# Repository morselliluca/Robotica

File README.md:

# Robotica

SE NON AVETE VOGLIA DI LEGGERE A FINE README CI SONO LE INFORMAZZIONI PER CONTTATARCI

Tutti i ptogetti robotica del Gruppo DKV Lab<br/>
Siamo un gruppo di 2 persone dell'Itis rossi che hanno partecipato alla Robocup per 4 anni consecutivi con questi progetti.<br/>
il gruppo è formato da:

	Luca Morselli
		-Arduino e Teensyduino:
			-Data collection -> lettura sensori di calore, ultrasuono, riflesso, encoder
			-Serial and comunication -> comunicazione in seriale tra arduino / teensy e Raspberry
			-Movement -> libreria e calibrazione driver e motori dc
		-Pcb design 
		-Mechanical part design
		
	Luca Barban:
		-On Raspberry:
			-Opencv -> riconoscimento caratteri e colori
			-Navigation -> navigazione della mappa
			-Mapping -> creazione della mappa partendo da ultrasuoni o lidar
			-Data Collection -> salvare i dati sulla mappa del nero calore lettere ecc.
			-Serial and comunication -> comunicazione in seriale tra arduino / teensy e Raspberry
			
Cosa troverete all'interno di questa repository:

All'interno di 1. lego line troverete (Line):

	/programmi
		Il codice per la rescue line per un EV3 della lego
		/programmi/Blocchi
			Dei Blocchi custom per leggere il riflesso RGB separatamente da i sensori Stock della lego

All'inerno di 2. project manta troverete (Maze):

	/documentazione
		Un foglio xsl (foglio di calcolo) con tutti i pinout dell'arduino mega, nano e raspberry 
		
	/pcb
		Le Pcb logic e Power usate per il robot + i file gerber per ordinarli
		
	/programma
		/programma/arduino
			/programma/arduino/mega
				il programma per l'arduino mega
			/programma/arduino/nano
				il programma per l'arduino nano
			/programma/arduino/test
				programmi di test vari
		
		/programma/rsby
			programma di test per la raspberry
	
	/scocca
		/scocca/3d
			pezzi da stampare 3d per la scocca (non utilizzati per l'ultima verisone )
		/scocca/logo
			il logo del team
		/scocca/ruote
			ruote da tagliare al laser (non le consiglio, compratele fatte bene Pololu o simili)
		/scocca/taglio
			la scocca del robot da tagliare al laser 
				bello = il piu recente
				manta = delle prove 
				cobra = il primo tentativo
				
	lista.xls 
		la lista dei pezzi che compongono il robot

All'inerno di 3. project Hive troverete (Maze):

	/cagacubi
		le varie versioni del hopper per buttare giu i cubi
		
	/documentazione
		la varia documentazione per tutti i pezzi del robot +  i vari modelli 3d + regole
	
	/foto
		delle foto del robot renderizzato
	
	/pcb 
		file pdf delle schematiche delle 2 pcb del robot + i file gerber per ordinarli
	
	/programma
		/programma/teensy
			il programma per la teensy per interfacciarsi a ros
		/programma/test
			test vari per la teensy e i sensori
	
	/ros documentation
		buona fortuna ragazzi, questo e l'unico pezzo di documentazione ti ros olte il sito ufficiale fatto da cani
	
	/scocca
		disegni di fuzion della scocca del robot per il taglio a laser
	
	/taglio
		progetti in dxf pronti per il taglio laser
		
	Lista.xls
		la lista dei pezzi che compongono il robot

All'inerno di 4. project Help troverete (Line, in aiuto al team A.L.D.O. per i modniali di robotica):

	/La scocca in 3d per la line
	
	/I modelli dai pezzi scelti

Faq:

E presente anche una ide di arduino munita di Teensyduino, rosserial e tutte le librerie da noi utilizzate.

Le parti di raspberry degli ultimi 2 progetti mancano e verra aggiunta solo quella dell'ultimo progetto in quanto quella di Manta e stata persa.

I pezzi per il taglio laser sono stati provati principalmente in legno (pippo), plexiglass ed alluminio

I pezzi stampati sono sati stampati solo con stampanti 3d a filamento in quanto della a resina non funzionava (prusa MK.3)

Il grosso dei pezzi e stato acquistato da Aliexpress

Nella lista di Manta ci sono i driver dei motori cinesi NON COMPRATELI si bruciano subito prendete i pololu anche se costano di piu valgono la spesa

Non usate amg8833 come in Manta costano tanto e non e possibile cambiare l'indirizzo i2c nella libreria per leggerli in maniera semplice noi abbiamo usato 2 arduini in piu per questo motvo (i nano), la soluzione migliore e acquistare gli mlx90614

Le batterie consiglio Lipo o 18650 almeno una 3s per portare la tensione intorno i 12v () noi usiamo 2 2s in serie

Consiglio di usare ruote e non cingoli

Consiglio motori con encoder tornano utili per contare i giri che ha fatto la ruota

Per collegare raspberry ad arduino o simili usate la seriale e usate direttamente la porta USB poer evitare di bruciarlo in quanto la maggior parte degli arduino sono a 5v e la raspby supporta solo 3.3v

Quando usate i driver della pololu come MC33926 portate il pin EN -> HIGH e i pin PWM(Negato)/D1 -> Low

I pin INA e INB sono usati per la direzione, vanno messi uno in HIGH uno in LOW 

Da prova_v17 sul progetto Hive le funzioni hanno un timing e vengono eseguite esattamente ogni N millisecondi (la funzione si trova all'interno del void loop)<br/>
	-Odom viene mandata 100HZ<br/>
	-velocita e encoder sono calcolati 1000HZ<br/>

Source:<br/>

Sensori di distanza arduino:<br/>
https://www.youtube.com/watch?v=6F1B_N6LuKw<br/>
https://dronebotworkshop.com/hc-sr04-ultrasonic-distance-sensor-arduino/<br/>

Libreria Pololu vnh5019, la base della libreria custom che troverete in/arduino-1.8.19/libraries/DriverDkv<br/>
https://github.com/pololu/dual-vnh5019-motor-shield<br/>
	
Tutorial per Rosserail + navigation:<br/>
https://www.youtube.com/watch?v=q1u_cC-5Sac<br/>
https://www.youtube.com/watch?v=HLLmV9LQoac<br/>

Ros in generale:<br/>
http://hotblackrobotics.github.io<br/>
https://automaticaddison.com<br/>

Ros navigation:<br/>
https://emanual.robotis.com/docs/en/platform/turtlebot3/learn/#books<br/>
http://wiki.ros.org/ROS/Installation<br/>
http://wiki.ros.org/catkin/Tutorials/create_a_workspace<br/>
http://wiki.ros.org/navigation/Tutorials/RobotSetup<br/>
http://wiki.ros.org/teb_local_planner<br/>
https://answers.ros.org/question/249216/rosserial-posearray-crashes-when-more-than-8-poses-are-used/<br/>

Mlx90614 come usarle e cambiare indirizzo:<br/>
https://www.instructables.com/Multiple-IR-Temperature-Sensors/<br/>
	
Il software per disegnare pcb che consiglio::<br/>
https://easyeda.com/editor<br/>
		
Dove ordinare le pcb online:<br/>
https://jlcpcb.com/<br/>
		
Dove ho ordinato i pezzi tagliati al laser in alluminio:<br/>
https://www.laserboost.com/en/create<br/>
	
Arduino ide (non la 2.0 che non funziona con teensyduino):<br/>
https://www.arduino.cc/en/software<br/>
			
Teensyduino:<br/>
https://www.pjrc.com/teensy/td_usage.html<br/>
https://www.pjrc.com/teensy/teensyduino.html<br/>
https://www.pjrc.com/teensy/td_pulse.html<br/>
https://www.pjrc.com/teensy/td_digital.html<br/>
https://www.pjrc.com/teensy/td_serial.html<br/>
https://www.pjrc.com/teensy/td_uart.html<br/>
		
Software Modellazione 3d (Fusion360 e gratis per gli studenti):<br/>	
https://www.autodesk.com/products/fusion-360/free-trial<br/>

NOTA:<br/>
Usare in maniera informativa nessuno di questi progetti e perfetto ma possono essere usati come una buona base per capire il funzionamento dei vari componenti<br/>
Siamo felici di aiutarvi per qualunque dubbio o perplessita<br/>

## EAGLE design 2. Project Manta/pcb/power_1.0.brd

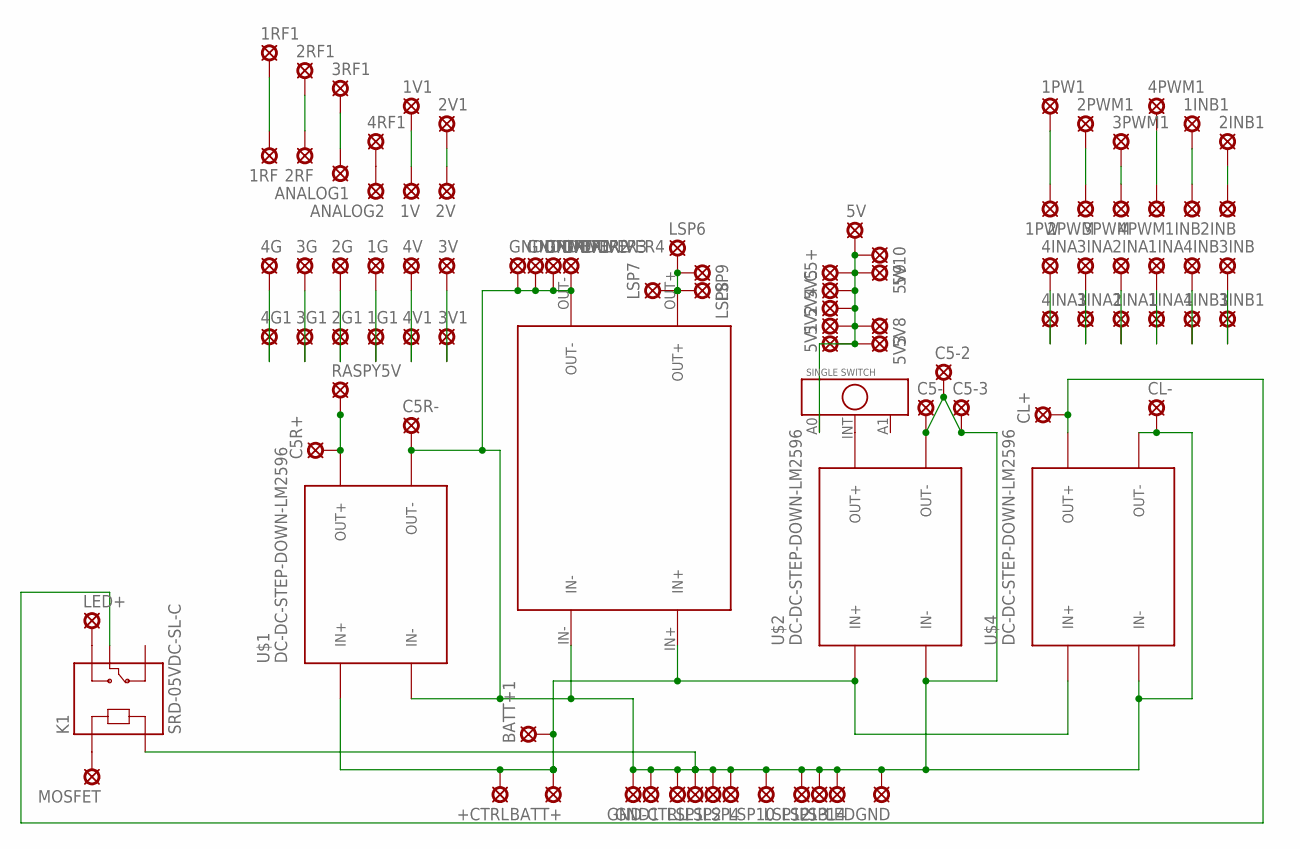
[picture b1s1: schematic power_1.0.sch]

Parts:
1G, 1G1, 1INA, 1INA1, 1INB, 1INB1, 1PW, 1PW1, 1RF, 1RF1, 1V, 1V1, 2G, 2G1, 2INA, 2INA1, 2INB, 2INB1, 2PWM, 2PWM1, 2RF, 2RF1, 2V, 2V1, 3G, 3G1, 3INA, 3INA1, 3INB, 3INB1, 3PWM, 3PWM1, 3RF1, 3V, 3V1, 4G, 4G1, 4INA, 4INA1, 4INB, 4INB1, 4PWM, 4PWM1, 4RF1, 4V, 4V1, 5V, 5V1, 5V2, 5V3, 5V4, 5V5, 5V8, 5V9, 5V10: LSP10
+CTRL: LSP10
-CTRL: LSP10
ANALOG1, ANALOG2: LSP10
BATT+, BATT+1: SE14
C5+, C5-, C5-2, C5-3, C5R+, C5R-: LSP10
CL+: LSP10
CL-: LSP10
GND, GND1: SE14
GNDDRIVER1, GNDDRIVER2, GNDDRIVER3, GNDDRIVER4: SE14
K1: SRD-05VDC-SL-C; RELAY_SRD-05VDC-SL-C
LED+: SE14
LEDGND: SE14
LSP1, LSP2, LSP4, LSP10, LSP12, LSP13, LSP14: LSP10
LSP6, LSP7, LSP8, LSP9: SE14
MOSFET: LSP10
RASPY5V: LSP10
U$1, U$2, U$4: DC-DC-STEP-DOWN-LM2596
U$3: DC-DCSTEPUP/DOWNBUCKCONVERTER
U$5: SINGE_SWITCH; SINGLE_SWITCH

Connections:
GND: -CTRL.MP, C5-.MP, C5-2.MP, C5-3.MP, C5R-.MP, CL-.MP, GND.MP, GND1.MP, GNDDRIVER1.MP, GNDDRIVER2.MP, GNDDRIVER3.MP, GNDDRIVER4.MP, K1.A2, LEDGND.MP, LSP1.MP, LSP2.MP, LSP4.MP, LSP10.MP, LSP12.MP, LSP13.MP, LSP14.MP, U$1.IN-, U$1.OUT-, U$2.IN-, U$2.OUT-, U$3.IN-, U$3.OUT-, U$4.IN-, U$4.OUT-
unnamed: U$2.OUT+, U$5.INT
unnamed: LSP6.MP, LSP7.MP, LSP8.MP, LSP9.MP, U$3.OUT+
unnamed: C5R+.MP, RASPY5V.MP, U$1.OUT+
unnamed: 5V.MP, 5V1.MP, 5V2.MP, 5V3.MP, 5V4.MP, 5V5.MP, 5V8.MP, 5V9.MP, 5V10.MP, C5+.MP, U$5.A0
unnamed: 4G.MP, 4G1.MP
unnamed: 3G.MP, 3G1.MP
unnamed: 2G.MP, 2G1.MP
unnamed: 1G.MP, 1G1.MP
unnamed: 4V.MP, 4V1.MP
unnamed: 3V.MP, 3V1.MP
unnamed: 2V.MP, 2V1.MP
unnamed: 1V.MP, 1V1.MP
unnamed: 4RF1.MP, ANALOG2.MP
unnamed: 3RF1.MP, ANALOG1.MP
unnamed: 2RF.MP, 2RF1.MP
unnamed: 1RF.MP, 1RF1.MP
unnamed: 1PW.MP, 1PW1.MP
unnamed: 2PWM.MP, 2PWM1.MP
unnamed: 4INA.MP, 4INA1.MP
unnamed: 3INA.MP, 3INA1.MP
unnamed: 2INA.MP, 2INA1.MP
unnamed: 1INA.MP, 1INA1.MP
unnamed: 4INB.MP, 4INB1.MP
unnamed: 3INB.MP, 3INB1.MP
unnamed: 3PWM.MP, 3PWM1.MP
unnamed: 4PWM.MP, 4PWM1.MP
unnamed: 1INB.MP, 1INB1.MP
unnamed: 2INB.MP, 2INB1.MP
unnamed: K1.NO, LED+.MP
unnamed: K1.A1, MOSFET.MP
unnamed: CL+.MP, K1.COM, U$4.OUT+
unnamed: +CTRL.MP, BATT+.MP, BATT+1.MP, U$1.IN+, U$2.IN+, U$3.IN+, U$4.IN+

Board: 2 copper layers, 96 parts (0 on the bottom side), 33 nets, no tracks yet.

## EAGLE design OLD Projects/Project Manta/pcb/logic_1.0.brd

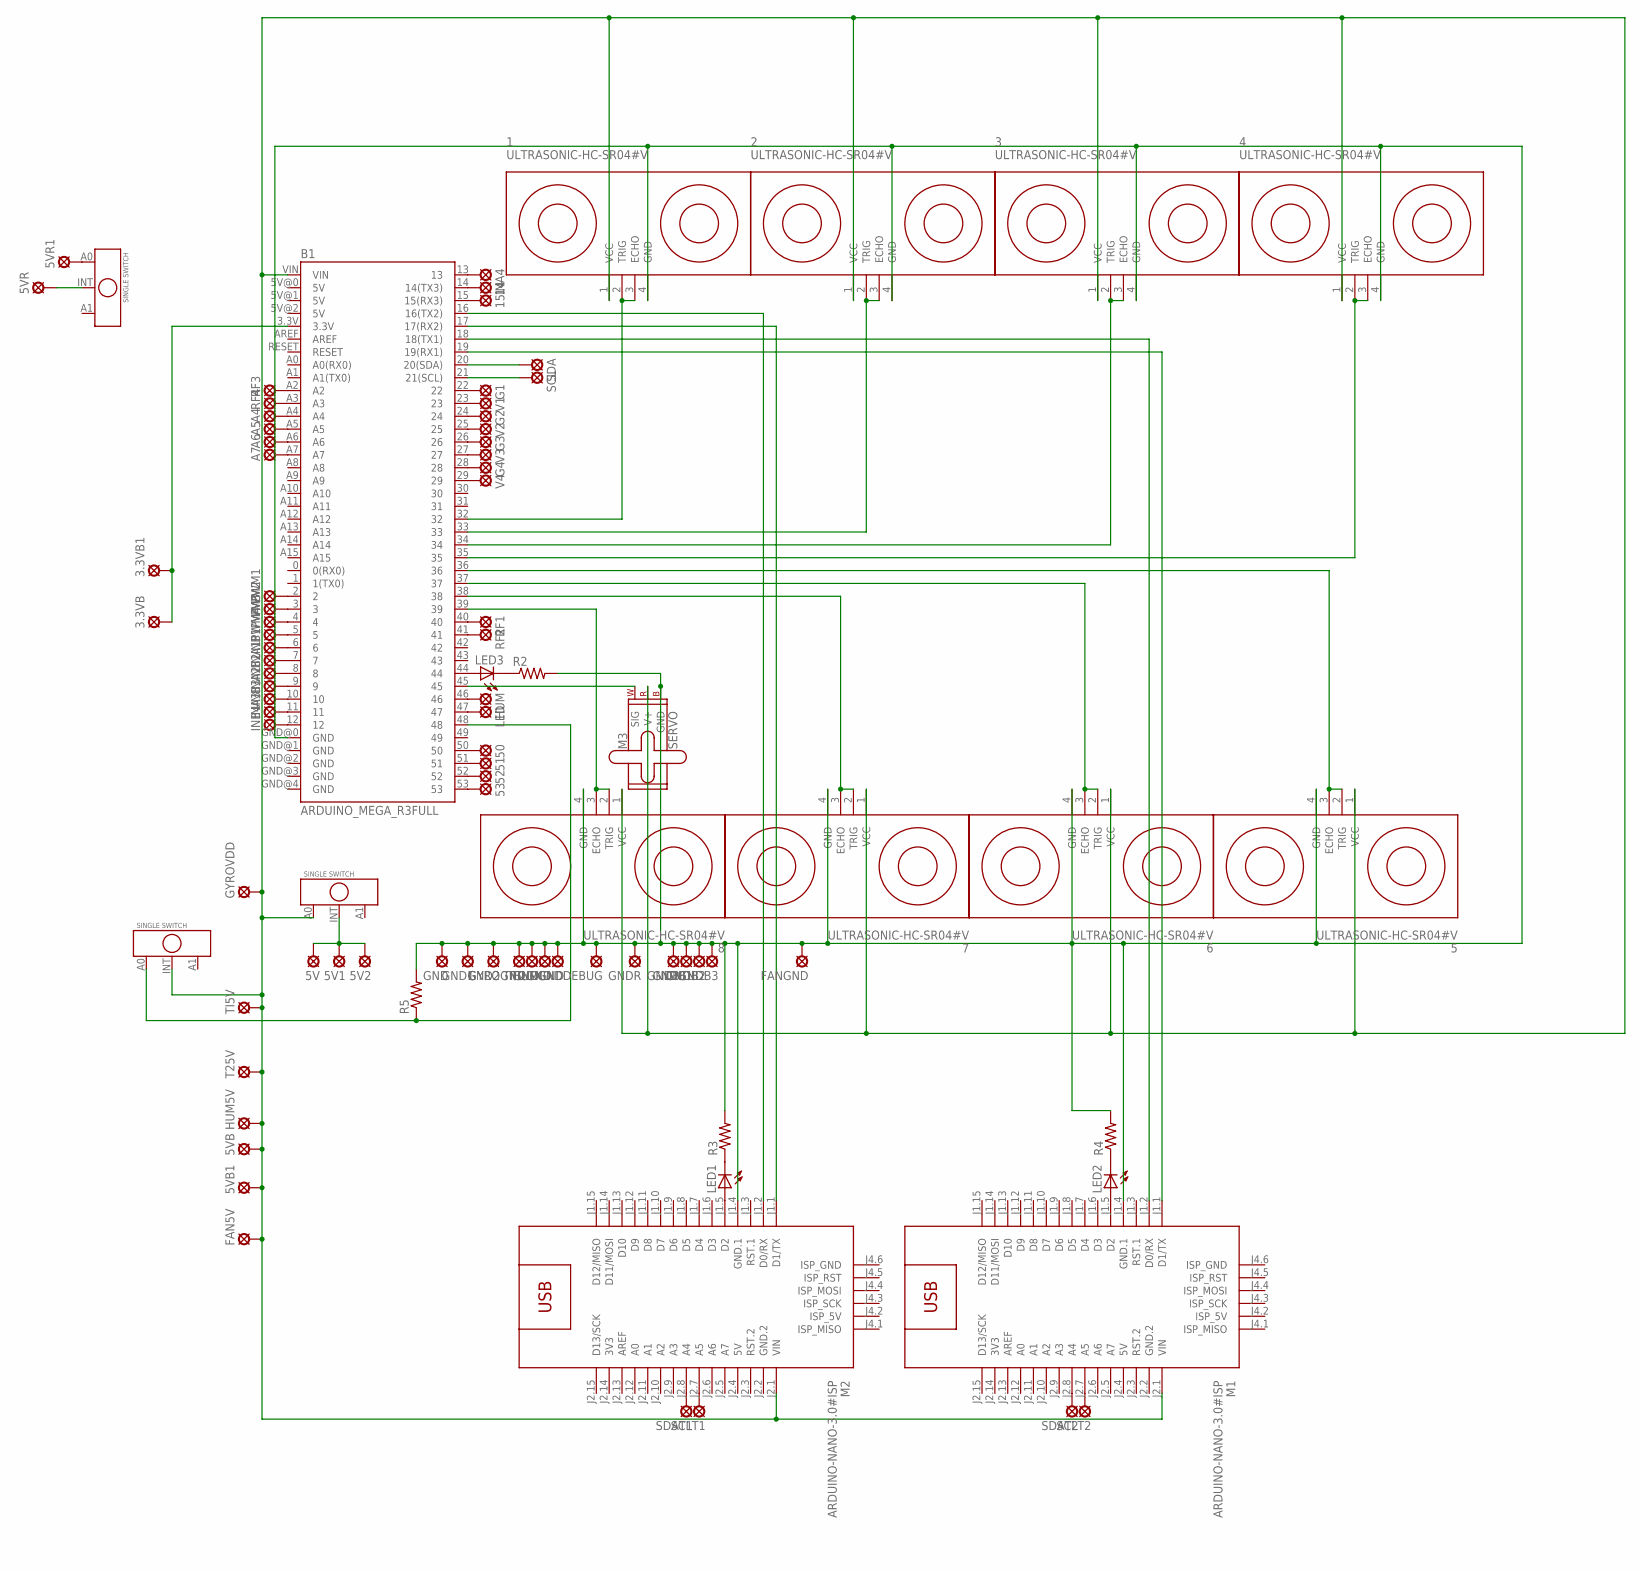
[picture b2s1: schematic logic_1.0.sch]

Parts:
1, 2, 3, 4, 5, 6, 7, 8: ULTRASONIC-HC-SR04#V
3.3VB, 3.3VB1, 5V, 5V1, 5V2, 5VB, 5VB1, 5VR, 5VR1, 14, 15, 50, 51, 52, 53: LSP10
A4, A5, A6, A7: LSP10
B1: ARDUINO_MEGA_R3FULL; ARDUINO_MEGA
FAN5V: LSP10
FANGND: LSP10
G1, G2, G3, G4: LSP10
GND, GND1, GND2: LSP10
GNDB, GNDB1, GNDB2, GNDB3: LSP10
GNDDEBUG: LSP10
GNDR: LSP10
GYROGND: LSP10
GYROVDD: LSP10
HUM, HUM5V: LSP10
HUMGND: LSP10
INA1, INA2, INA3, INA4: LSP10
INB1, INB2, INB3, INB4: LSP10
LED: LSP10
LED1, LED2, LED3: LED5MM
M1, M2: ARDUINO-NANO-3.0#ISP
M3: SERVO; 1X03
PWM1, PWM2, PWM3, PWM4: LSP10
R2, R3, R4, R5: R-US_0207/10; 0207/10
RF1, RF2, RF3, RF4: LSP10
SCL: LSP10
SCLT1, SCLT2: LSP10
SDA: LSP10
SDAT1, SDAT2: LSP10
T2GND, T25V: LSP10
TI5V: LSP10
TIGND: LSP10
U$1, U$2, U$3: SINGE_SWITCH; SINGLE_SWITCH
V1, V2, V3, V4: LSP10

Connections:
3V3: M1.J2.14 (3V3), M2.J2.14 (3V3)
5V: M1.J2.4 (5V), M2.J2.4 (5V)
GND: 1.4 (GND), 2.4 (GND), 3.4 (GND), 4.4 (GND), 5.4 (GND), 6.4 (GND), 7.4 (GND), 8.4 (GND), B1.GND@0 (GND), FANGND.MP, GND.MP, GND1.MP, GND2.MP, GNDB.MP, GNDB1.MP, GNDB2.MP, GNDB3.MP, GNDDEBUG.MP, GNDR.MP, GYROGND.MP, HUMGND.MP, M1.J1.4 (GND.1), M2.J1.4 (GND.1), M3.3 (GND), R2.2, R3.2, R4.2, R5.2, T2GND.MP, TIGND.MP
GND.2: M1.J2.2 (GND.2), M2.J2.2 (GND.2)
unnamed: 5VR1.MP, U$2.A0
unnamed: 5V.MP, 5V1.MP, 5V2.MP, U$1.INT
unnamed: B1.2, PWM1.MP
unnamed: B1.16 (16(TX2)), M2.J1.2 (D0/RX)
unnamed: B1.17 (17(RX2)), M2.J1.1 (D1/TX)
unnamed: B1.18 (18(TX1)), M1.J1.2 (D0/RX)
unnamed: B1.19 (19(RX1)), M1.J1.1 (D1/TX)
unnamed: 1.2 (TRIG), 1.3 (ECHO), B1.32
unnamed: 2.2 (TRIG), 2.3 (ECHO), B1.33
unnamed: 3.2 (TRIG), 3.3 (ECHO), B1.34
unnamed: 4.2 (TRIG), 4.3 (ECHO), B1.35
unnamed: 5.2 (TRIG), 5.3 (ECHO), B1.36
unnamed: 6.2 (TRIG), 6.3 (ECHO), B1.37
unnamed: 7.2 (TRIG), 7.3 (ECHO), B1.38
unnamed: 8.2 (TRIG), 8.3 (ECHO), B1.39
unnamed: B1.45, M3.1 (SIG)
unnamed: 1.1 (VCC), 2.1 (VCC), 3.1 (VCC), 4.1 (VCC), 5.1 (VCC), 5VB.MP, 5VB1.MP, 6.1 (VCC), 7.1 (VCC), 8.1 (VCC), B1.VIN, FAN5V.MP, GYROVDD.MP, HUM5V.MP, M1.J2.1 (VIN), M2.J2.1 (VIN), M3.2 (V+), T25V.MP, TI5V.MP, U$1.A0, U$3.INT
unnamed: B1.3, PWM2.MP
unnamed: B1.4, PWM3.MP
unnamed: B1.5, PWM4.MP
unnamed: B1.6, INB1.MP
unnamed: B1.7, INA1.MP
unnamed: B1.8, INB2.MP
unnamed: B1.9, INA2.MP
unnamed: B1.10, INB3.MP
unnamed: B1.11, INA3.MP
unnamed: B1.12, INB4.MP
unnamed: B1.13, INA4.MP
unnamed: B1.22, G1.MP
unnamed: B1.23, V1.MP
unnamed: B1.24, G2.MP
unnamed: B1.25, V2.MP
unnamed: B1.26, G3.MP
unnamed: B1.27, V3.MP
unnamed: B1.28, G4.MP
unnamed: B1.29, V4.MP
unnamed: B1.20 (20(SDA)), SDA.MP
unnamed: B1.21 (21(SCL)), SCL.MP
unnamed: B1.46, HUM.MP
unnamed: B1.47, LED.MP
unnamed: 3.3VB.MP, 3.3VB1.MP, B1.3.3V
unnamed: M2.J2.8 (A4), SDAT1.MP
unnamed: M2.J2.7 (A5), SCLT1.MP
unnamed: M1.J2.8 (A4), SDAT2.MP
unnamed: M1.J2.7 (A5), SCLT2.MP
unnamed: B1.40, RF1.MP
unnamed: B1.44, LED3.A
unnamed: B1.41, RF2.MP
unnamed: 5VR.MP, U$2.INT
unnamed: B1.A2, RF3.MP
unnamed: B1.A3, RF4.MP
unnamed: LED1.A, M2.J1.5 (D2)
unnamed: LED2.A, M1.J1.5 (D2)
unnamed: LED3.K (C), R2.1
unnamed: LED2.K (C), R4.1
unnamed: LED1.K (C), R3.1
unnamed: 50.MP, B1.50
unnamed: 51.MP, B1.51
unnamed: 52.MP, B1.52
unnamed: A6.MP, B1.A6
unnamed: A7.MP, B1.A7
unnamed: A4.MP, B1.A4
unnamed: A5.MP, B1.A5
unnamed: 53.MP, B1.53
unnamed: B1.48, R5.1, U$3.A0
unnamed: 14.MP, B1.14 (14(TX3))
unnamed: 15.MP, B1.15 (15(RX3))

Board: 2 copper layers, 92 parts (1 on the bottom side), 71 nets, no tracks yet.

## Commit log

2021-12-20 Version 1
2021-12-24 nuova scocca
2021-12-24 render
2021-12-31 sistemato roba
2022-01-22 change
2022-01-26 opsy
2022-02-02 test
2022-02-17 i cazzi miei
2022-03-12 putin
2022-03-12 mannaggia il putin
2022-03-12 put in gerber
2022-03-15 qualcosa
2022-03-21 bnhh
2022-03-22 ma perche cazzo per 2 minchiate devo fare un summary
2022-03-23 ancora summary inutili al pipo
2022-03-23 e ancora
2022-03-24 vnhbn
2022-03-27 spostato roba
2022-03-30 Schifo temporaneo ros
2022-04-02 sistemo
2022-04-05 cagacubi
2022-04-07 disegni
2022-04-07 YAML files for costmap and movebase
2022-04-18 pezzi
2022-04-20 Ros Magic
2022-04-29 foto
2022-05-05 premio
2022-05-05 finito tutto a parte la pinza
2022-05-29 taglio
2026-01-01 Remove warning about copying the robot
    Removed warning against copying the robot directly.

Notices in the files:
parts and their libraries:
diy-modmod: Released under the Creative Commons Attribution 4.0 International License: http://creativecommons.org/licenses/by/4.0
SparkFun-Boards: Licensing: Creative Commons ShareAlike 4.0 International - https://creativecommons.org/licenses/by-sa/4.0
